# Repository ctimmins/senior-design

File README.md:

# SENIOR DESIGN Fall 2014 - Winter 2015
##Various files for the projects throughout senior design
###Agricultural Monitoring System
Our senior design project
###Magnetometer
A silly little project in Fall quarter to establish i2c communication between a magnetometer and psoc5 dev kit
###Check out my [website](www.chadtimmins.com) for further updates!

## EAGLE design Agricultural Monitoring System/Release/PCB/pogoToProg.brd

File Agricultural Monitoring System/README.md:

<!-- START doctoc generated TOC please keep comment here to allow auto update -->
<!-- DON'T EDIT THIS SECTION, INSTEAD RE-RUN doctoc TO UPDATE -->
**Table of Contents**  *generated with [DocToc](https://github.com/thlorenz/doctoc)*

- [System for Temperature and Evapotranspiration Monitoring (STEM)](#system-for-temperature-and-evapotranspiration-monitoring-stem)
  - [Abstract](#abstract)
  - [Marketing Video](#marketing-video)
  - [Features/Components](#featurescomponents)
      - [PSoC5](#psoc5)
      - [Soil Sensors](#soil-sensors)
      - [Infrared Sensor](#infrared-sensor)
      - [XBee Wireless Radio](#xbee-wireless-radio)
      - [Battery System](#battery-system)
      - [Low Power Consumption](#low-power-consumption)
      - [Beaglebone Black](#beaglebone-black)
      - [Data Store](#data-store)
      - [Web Application and Synchronized Data](#web-application-and-synchronized-data)
      - [Analytics Framework](#analytics-framework)
  - [Future Improvements](#future-improvements)
  - [User Manual](#user-manual)
      - [STEM](#stem)
      - [Beaglebone](#beaglebone)
      - [Firebase](#firebase)
      - [Web Application](#web-application)

<!-- END doctoc generated TOC please keep comment here to allow auto update -->

#System for Temperature and Evapotranspiration Monitoring (STEM)

##Abstract
Monitoring plant health and conserving water are two important considerations in regards to agriculture, especially given the current drought. Plants take in water through rainfall and regular watering and lose water through transpiration. If growers can quantify the amount of water that is available to the plant and how much the plant loses through transpiration, they can irrigate more efficiently. STEM accomplishes both of these goals by monitoring soil moisture and temperature at different depths in the ground around a plant.  STEM also observes the leaf temperature of the plant, which correlates to whether or not the stomata are opened or closed and thus whether or not water is evaporating from the leaves.

The board in the field sends the captured data wirelessly to a coordinator which then uploads the data to a remote database.  From this point, growers can view the data using our web application on a computer or tablet.

##Marketing Video

##Drawings of Systems and Subsystems

##Features/Components
####PSoC5
32 bit ARM Cortex M0 based programmable system on chip a.k.a. the brains of each node.
####Soil Sensors
The multi-level installation of subterraneous sensors gives the user a soil moisture and temperature profile and is useful for monitoring the progression of the water-front.  In other words, our system is able to track how water flows through soil and the conditions that cause it do so.  The soil moisture sensors use transmission line techniques to acquire volumetric water content and are immune to inaccurate measurements due to varying levels of salinity.
####Infrared Sensor
The mounted infrared camera gives the user the ability to detect changes in leaf temperature as a function of time. This is used to determine when the stomates in the leaf closes in the day, which marks the point where the plant stops losing water.
####XBee Wireless Radio
XBee radios are low energy, low bandwidth radios that have a range of around 300 feet.
####Battery System
The device is powered by a 2500 mAh Li-po battery. The battery can be recharged through an external solar panel or a USB phone charger. A analog to digital converter is placed to measure the health of the battery, thereby alerting the user that the battery is low.
####Low Power Consumption
Sleep timers were implemented to reduce overall power consumption. The board itself wakes up roughly every 4 seconds, but only takes and transmits measurements periodically. The frequency of message transmittance is user defined and can easily be adjusted depending on the application.
####Beaglebone Black
We used TI’s Beaglebone Black as the XBee coordinator and internet gateway. An XBee radio was mounted to the Beaglebone and Python scripts were developed to handle all communication to and from the wireless sensors. It also maintains information about multiple nodes such as battery status, and various IR configuration settings. Additional scripts were developed for uploading our data to a secure database (Firebase).
The decision to go with a linux micro computer over Digi’s ConnectPort and proprietary Device Cloud was due to the difficulty of integrating a custom user interface with Digi’s services.
####Data Store
We used Firebase to collect and manage all data.  Firebase was chosen for its simplicity in uploading and retrieving data.  It also provides an easy to use dashboard to manage, view, and download all data.
####Web Application and Synchronized Data
Our web application, along with Firebase as a backend, serves as a simple alternative to Etherios Device Cloud.  Firebase and the relevant javascript API’s allow for real time data synchronization across devices.  This means the user can see live updates of sensor data without having to refresh the page. 
####Analytics Framework
TBD

##Future Improvements

##User Manual
####STEM

####Beaglebone

####Firebase

####Web Application

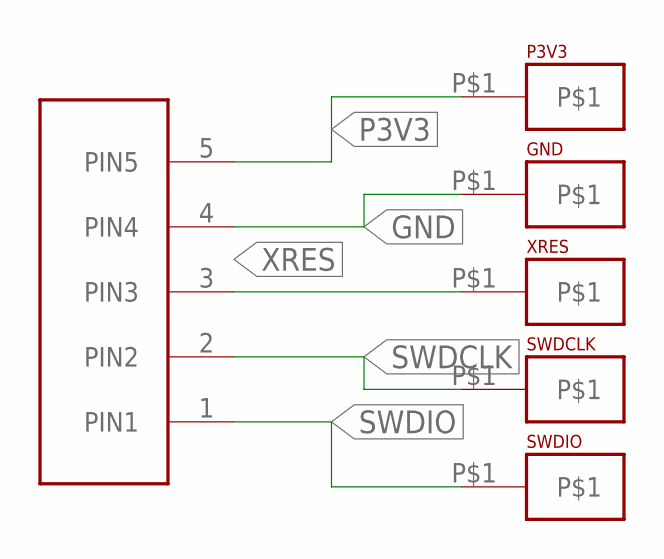
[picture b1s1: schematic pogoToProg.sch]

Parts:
GND: POGO-MATING
P3V3: POGO-MATING
SWDCLK: POGO-MATING
SWDIO: POGO-MATING
U$1: HEADER-5; NON-5
XRES: POGO-MATING

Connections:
GND: GND.P$1, U$1.4 (PIN4)
P3V3: P3V3.P$1, U$1.5 (PIN5)
SWDCLK: SWDCLK.P$1, U$1.2 (PIN2)
SWDIO: SWDIO.P$1, U$1.1 (PIN1)
XRES: U$1.3 (PIN3), XRES.P$1

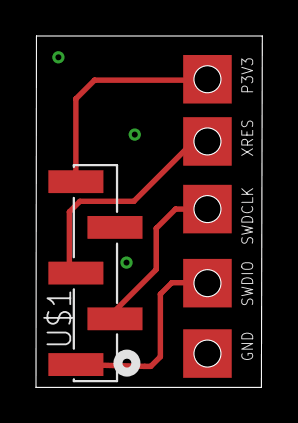
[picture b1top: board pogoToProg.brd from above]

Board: 2 copper layers, 12.6 x 19.5 mm, 6 parts (0 on the bottom side), 5 nets.

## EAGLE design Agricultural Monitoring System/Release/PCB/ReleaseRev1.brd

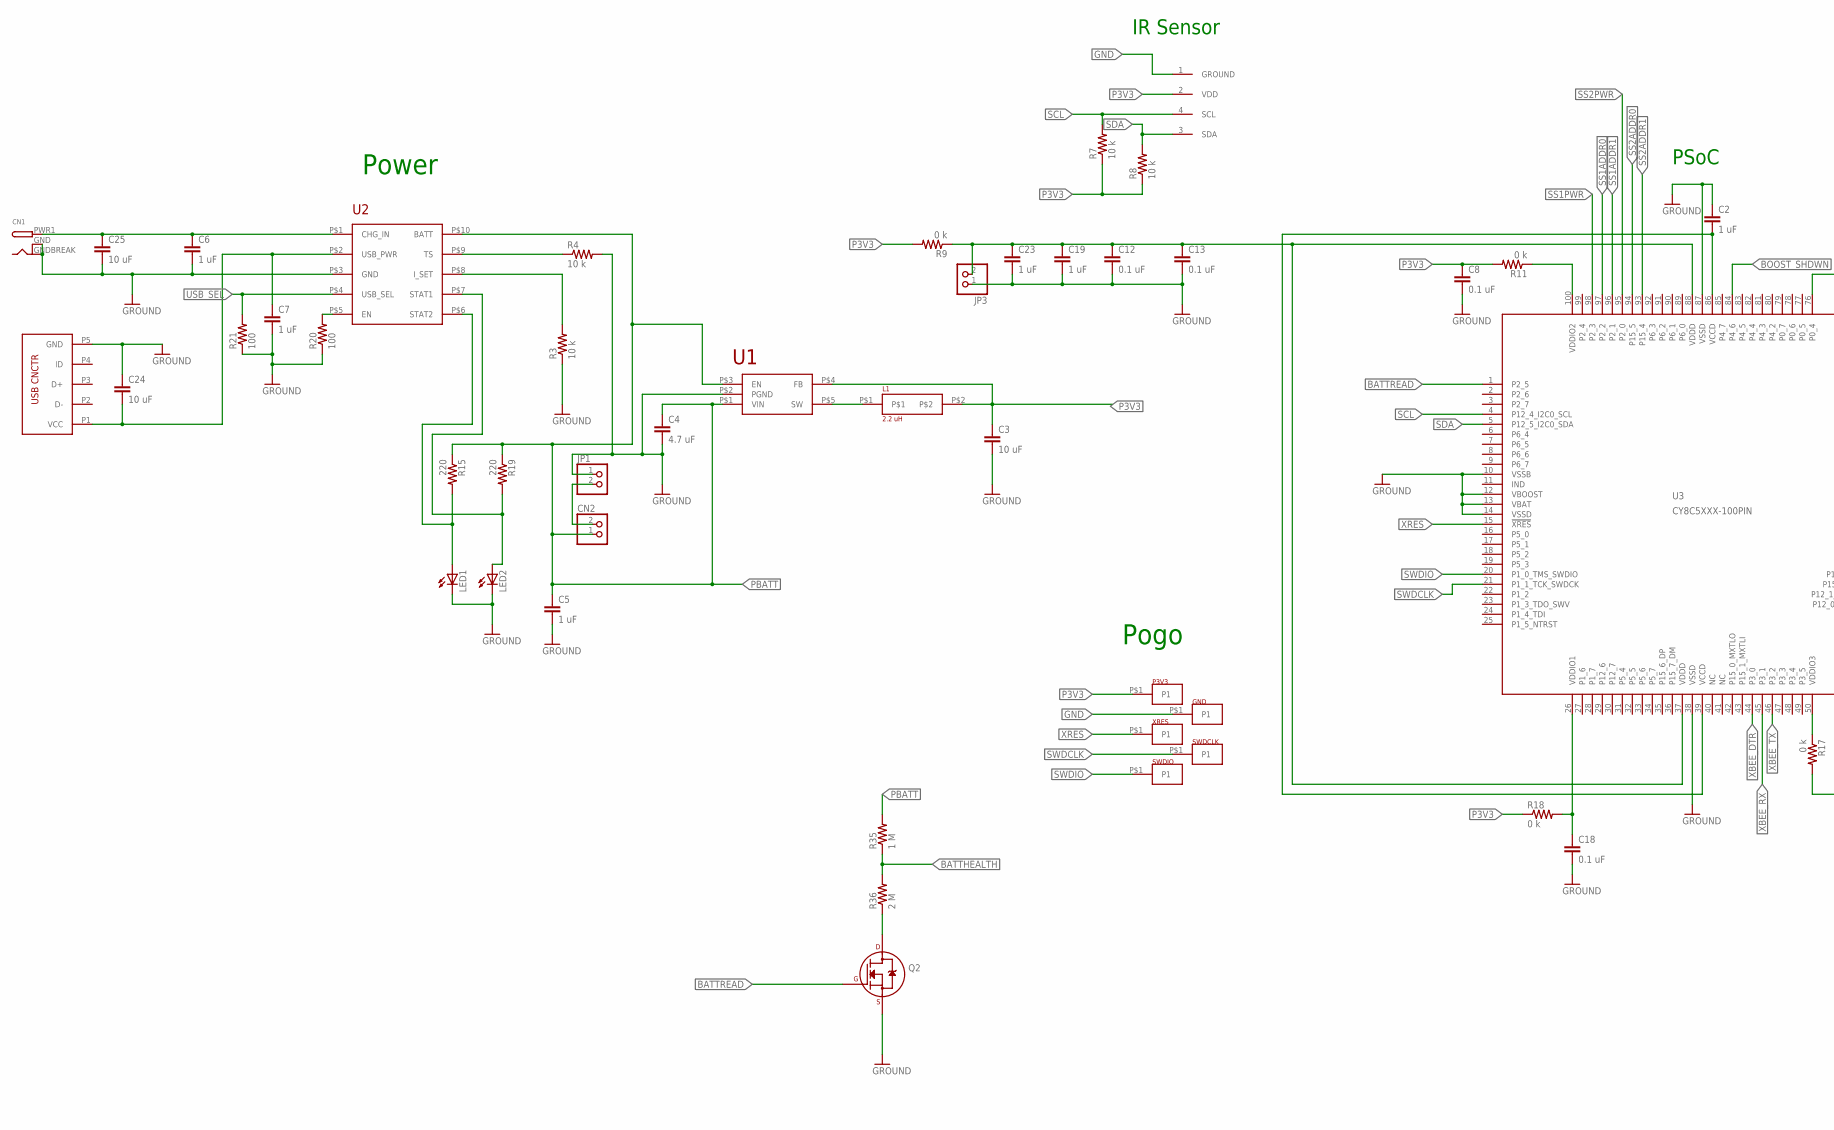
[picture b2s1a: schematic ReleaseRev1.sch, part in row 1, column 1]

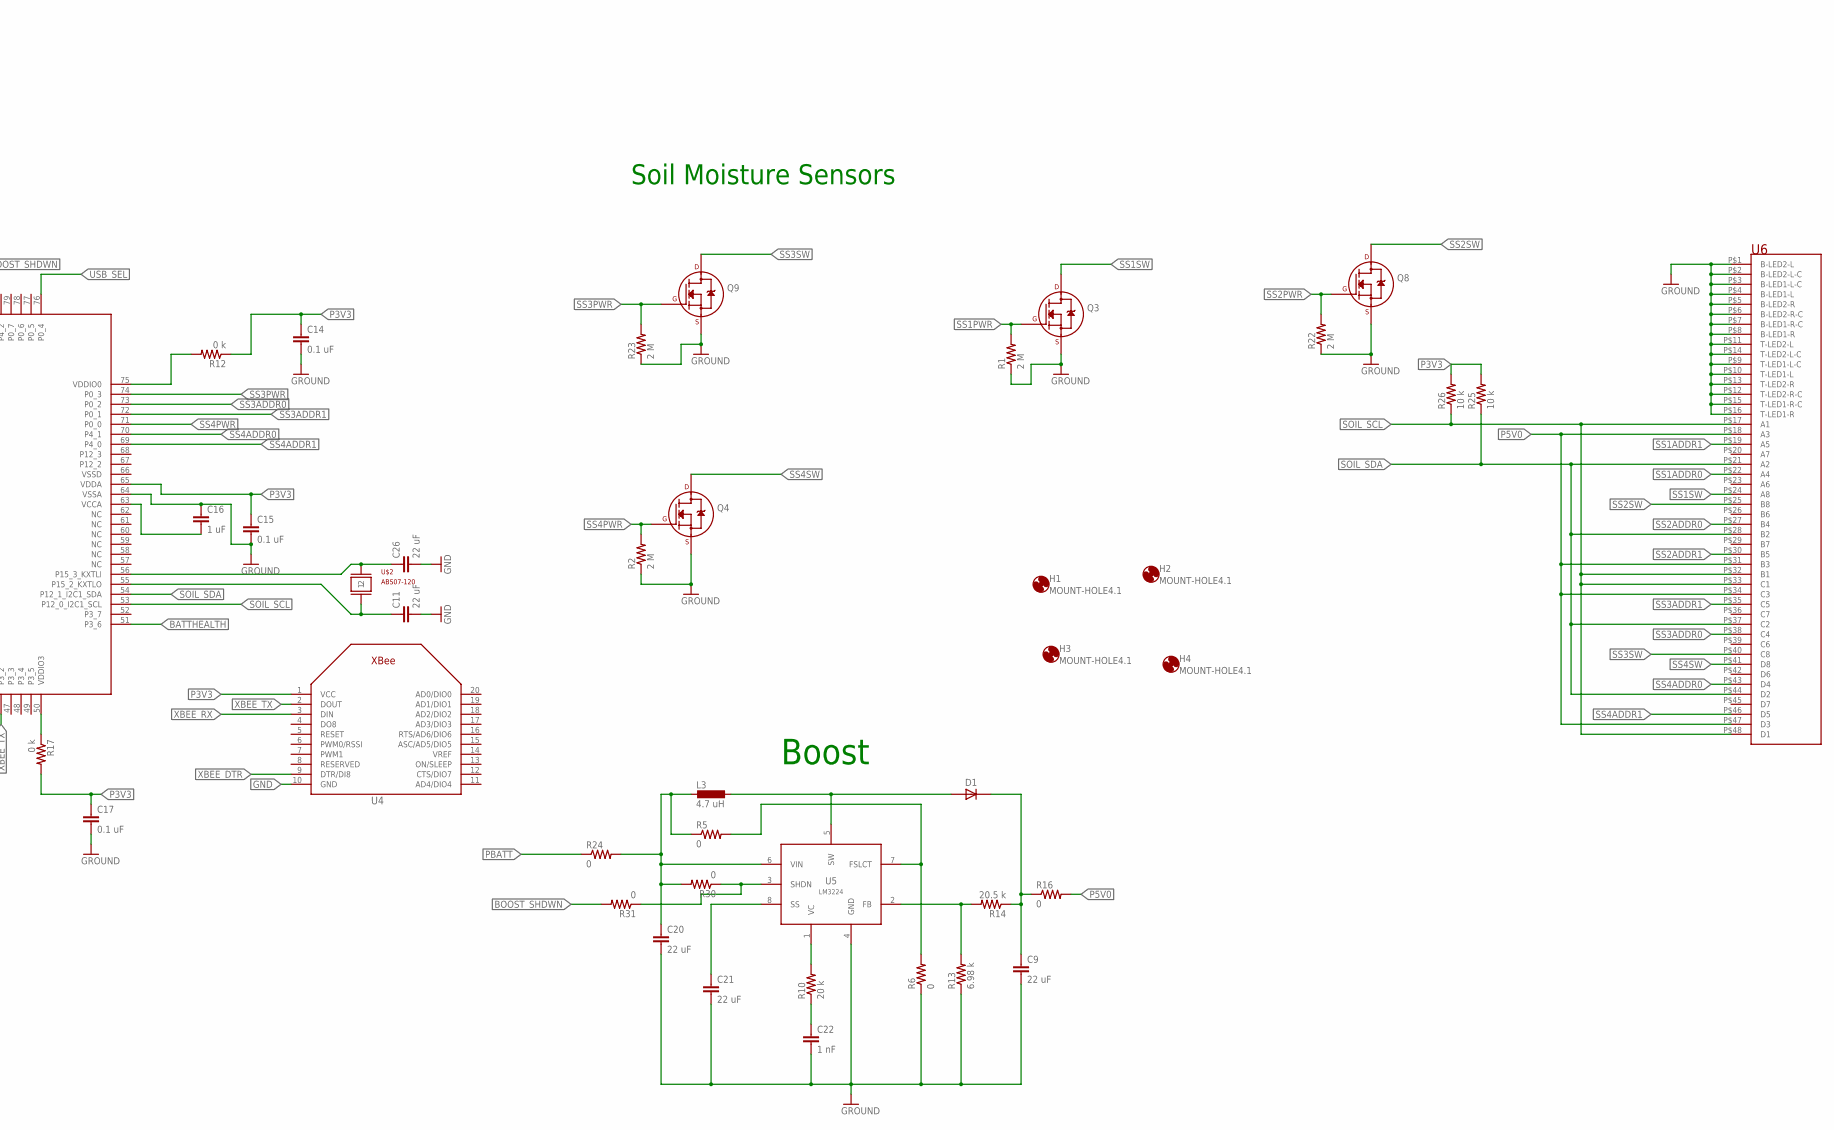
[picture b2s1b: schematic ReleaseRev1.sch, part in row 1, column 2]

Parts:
C2, C5, C6, C7, C16, C19, C23: 1 uF; 0603
C3, C24, C25: 10 uF; 0603
C4: 4.7 uF; 0603
C8, C12, C13, C14, C15, C17, C18: 0.1 uF; 0603
C9, C11, C20, C21, C26: 22 uF; 0603
C22: 1 nF; 0603
CN1: DCBARRELSMT; DCJACK_2MM_SMT
CN2: JST_2PIN-SMT-RA; JST-PH-2-SMT-RA
D1: DIODE; 0603-LED
GND: POGO-MOUNTING
H1, H2, H3, H4: MOUNT-HOLE4.1; 4,1
IRSENSOR: TO39
JP1, JP3: PINHD-1X2; 1X02
L1: LPO3310
L3: 4.7 uH; DO3316P
LED1, LED2: LEDCHIP-LED0603; CHIP-LED0603
P3V3: POGO-MOUNTING
Q2, Q3, Q4, Q8, Q9: 2N7000_SOT23; SOT-23
R1, R2, R22, R23, R36: 2 M; 0603
R3, R4, R7, R8, R25, R26: 10 k; 0603
R5, R6, R30, R31: 0; 0603
R9, R11, R12, R17, R18: 0 k; 0603
R10: 20 k; 0603
R13: 6.98 k; 0603
R14: 20.5 k; 0603
R15, R19: 220; 0603
R16, R24: 0; R2010
R20, R21: 100; 0603
R35: 1 M; 0603
SWDCLK: POGO-MOUNTING
SWDIO: POGO-MOUNTING
U1: LM3671-407564
U2: LM3658
U3: CY8C5XXX-100PIN; TQFP-14X14-100
U4: XBEE
U5: LM3224; MSOP-8
U6: RJSAE-5380-04
U$1: FCI10118192-0001LF
U$2: ABS07-120; 2-SMD
XRES: POGO-MOUNTING

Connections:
BATTHEALTH: R35.1, R36.2, U3.51 (P3_6)
BATTREAD: Q2.1 (G), U3.1 (P2_5)
BOOST_SHDWN: R31.2, U3.84 (P4_6)
GND: C2.1, C3.2, C4.2, C5.2, C6.2, C7.2, C8.2, C9.2, C11.2, C12.2, C13.2, C14.2, C15.2, C16.1, C17.2, C18.2, C19.2, C20.2, C21.2, C22.2, C23.2, C24.1, C25.2, C26.2, CN1.GND (GNDBREAK), CN1.GNDBREAK (GND), GND.P$1, IRSENSOR.1 (GROUND), JP1.1, JP3.1, LED1.C, LED2.C, Q2.2 (S), Q3.2 (S), Q4.2 (S), Q8.2 (S), Q9.2 (S), R1.1, R2.1, R3.1, R4.2, R6.1, R13.1, R20.1, R21.1, R22.1, R23.1, U1.P$2 (PGND), U2.P$3 (GND), U3.10 (VSSB), U3.12 (VBOOST), U3.13 (VBAT), U3.14 (VSSD), U3.38 (VSSD), U3.64 (VSSA), U3.87 (VSSD), U4.10 (GND), U5.4 (GND), U6.P$1 (B-LED2-L), U6.P$2 (B-LED2-L-C), U6.P$3 (B-LED1-L-C), U6.P$4 (B-LED1-L), U6.P$5 (B-LED2-R), U6.P$6 (B-LED2-R-C), U6.P$7 (B-LED1-R-C), U6.P$8 (B-LED1-R), U6.P$9 (T-LED1-L-C), U6.P$10 (T-LED1-L), U6.P$11 (T-LED2-L), U6.P$12 (T-LED2-R-C), U6.P$13 (T-LED2-R), U6.P$14 (T-LED2-L-C), U6.P$15 (T-LED1-R-C), U6.P$16 (T-LED1-R), U$1.P5 (GND)
unnamed: R20.2, U2.P$5 (EN)
unnamed: R3.2, U2.P$8 (I_SET)
unnamed: C21.1, U5.8 (SS)
unnamed: C26.1, U3.56 (P15_3_KXTLI), U$2.1
unnamed: C6.1, C25.1, CN1.PWR1 (PWR), U2.P$1 (CHG_IN)
unnamed: C18.1, R18.2, U3.26 (VDDIO1)
unnamed: D1.A, L3.2, U5.5 (SW)
unnamed: R4.1, U2.P$9 (TS)
unnamed: R10.2, U5.1 (VC)
unnamed: CN2.2 (1), JP1.2
unnamed: C22.1, R10.1
unnamed: R13.2, R14.2, U5.2 (FB)
unnamed: C2.2, U3.39 (VCCD), U3.86 (VCCD)
unnamed: Q2.3 (D), R36.1
unnamed: C16.2, U3.63 (VCCA)
unnamed: R5.2, R6.2, U5.7 (FSLCT)
unnamed: C11.1, U3.55 (P15_2_KXTLO), U$2.2
unnamed: R12.2, U3.75 (VDDIO0)
unnamed: R11.1, U3.100 (VDDIO2)
unnamed: C12.1, C13.1, C19.1, C23.1, JP3.2, R9.1, U3.37 (VDDD), U3.88 (VDDD)
unnamed: R17.1, U3.50 (VDDIO3)
unnamed: LED2.A, R19.2, U2.P$7 (STAT1)
unnamed: LED1.A, R15.2, U2.P$6 (STAT2)
unnamed: L1.P$1, U1.P$5 (SW)
unnamed: R30.1, R31.1, U5.3 (SHDN)
P: C20.1, L3.1, R5.1, R24.2, R30.2, U5.6 (VIN)
P3V3: C3.1, C8.1, C14.1, C15.1, C17.1, IRSENSOR.2 (VDD), L1.P$2, P3V3.P$1, R7.1, R8.1, R9.2, R11.2, R12.1, R17.2, R18.1, R25.2, R26.2, U1.P$4 (FB), U3.65 (VDDA), U4.1 (VCC)
P5: C9.1, D1.C, R14.1, R16.1
P5V0: R16.2, U6.P$18 (A3), U6.P$31 (B3), U6.P$34 (C3), U6.P$47 (D3)
PBATT: C4.1, C5.1, CN2.1 (2), R15.1, R19.1, R24.1, R35.2, U1.P$1 (VIN), U1.P$3 (EN), U2.P$10 (BATT)
SCL: IRSENSOR.4 (SCL), R7.2, U3.4 (P12_4_I2C0_SCL)
SDA: IRSENSOR.3 (SDA), R8.2, U3.5 (P12_5_I2C0_SDA)
SOIL_SCL: R26.1, U3.53 (P12_0_I2C1_SCL), U6.P$17 (A1), U6.P$32 (B1), U6.P$33 (C1), U6.P$48 (D1)
SOIL_SDA: R25.1, U3.54 (P12_1_I2C1_SDA), U6.P$21 (A2), U6.P$28 (B2), U6.P$37 (C2), U6.P$44 (D2)
SS1ADDR0: U3.97 (P2_2), U6.P$22 (A4)
SS1ADDR1: U3.96 (P2_1), U6.P$19 (A5)
SS1PWR: Q3.1 (G), R1.2, U3.98 (P2_3)
SS1SW: Q3.3 (D), U6.P$24 (A8)
SS2ADDR0: U3.94 (P15_5), U6.P$27 (B4)
SS2ADDR1: U3.93 (P15_4), U6.P$30 (B5)
SS2PWR: Q8.1 (G), R22.2, U3.95 (P2_0)
SS2SW: Q8.3 (D), U6.P$25 (B8)
SS3ADDR0: U3.73 (P0_2), U6.P$38 (C4)
SS3ADDR1: U3.72 (P0_1), U6.P$35 (C5)
SS3PWR: Q9.1 (G), R23.2, U3.74 (P0_3)
SS3SW: Q9.3 (D), U6.P$40 (C8)
SS4ADDR0: U3.70 (P4_1), U6.P$43 (D4)
SS4ADDR1: U3.69 (P4_0), U6.P$46 (D5)
SS4PWR: Q4.1 (G), R2.2, U3.71 (P0_0)
SS4SW: Q4.3 (D), U6.P$41 (D8)
SWDCLK: SWDCLK.P$1, U3.21 (P1_1_TCK_SWDCK)
SWDIO: SWDIO.P$1, U3.20 (P1_0_TMS_SWDIO)
USB: C7.1, C24.2, U2.P$2 (USB_PWR), U$1.P1 (VCC)
USB_SEL: R21.2, U2.P$4 (USB_SEL), U3.76 (P0_4)
XBEE_DTR: U3.44 (P3_0), U4.9 (DTR/DI8)
XBEE_RX: U3.45 (P3_1), U4.3 (DIN)
XBEE_TX: U3.46 (P3_2), U4.2 (DOUT)
XRES: U3.15 (!XRES!), XRES.P$1

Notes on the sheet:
PSoC
IR Sensor
Boost
Pogo
Power
Soil Moisture Sensors

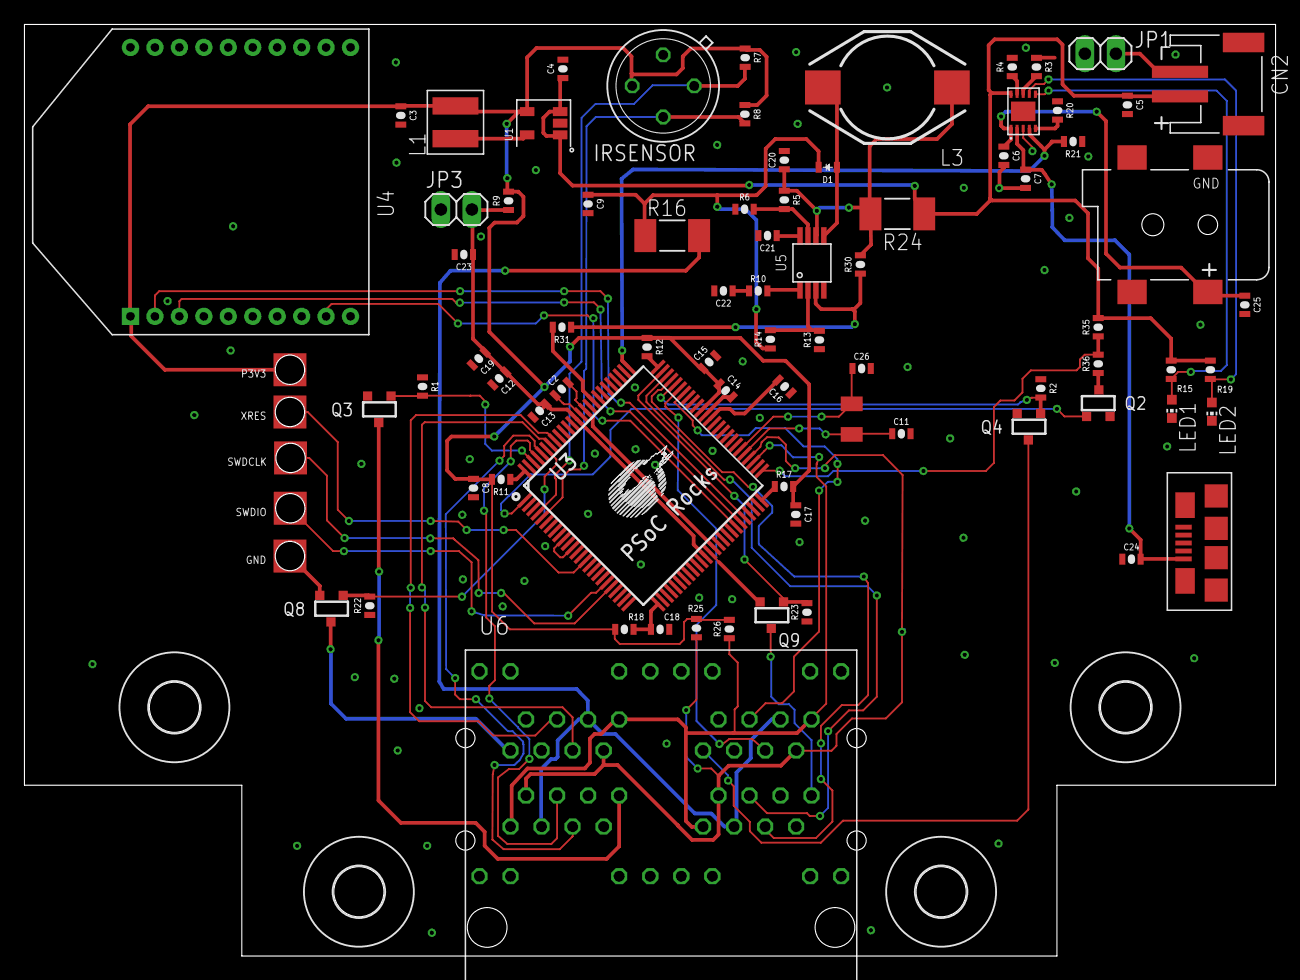
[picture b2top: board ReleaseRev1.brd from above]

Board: 2 copper layers, 102.3 x 76.2 mm, 86 parts (0 on the bottom side), 62 nets.

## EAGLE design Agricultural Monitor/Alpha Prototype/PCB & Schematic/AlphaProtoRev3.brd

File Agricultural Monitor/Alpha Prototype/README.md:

#Alpha Prototype
##The first hardware prototype of the agricultural monitoring system
###Bill of Materials

###PCB Layout

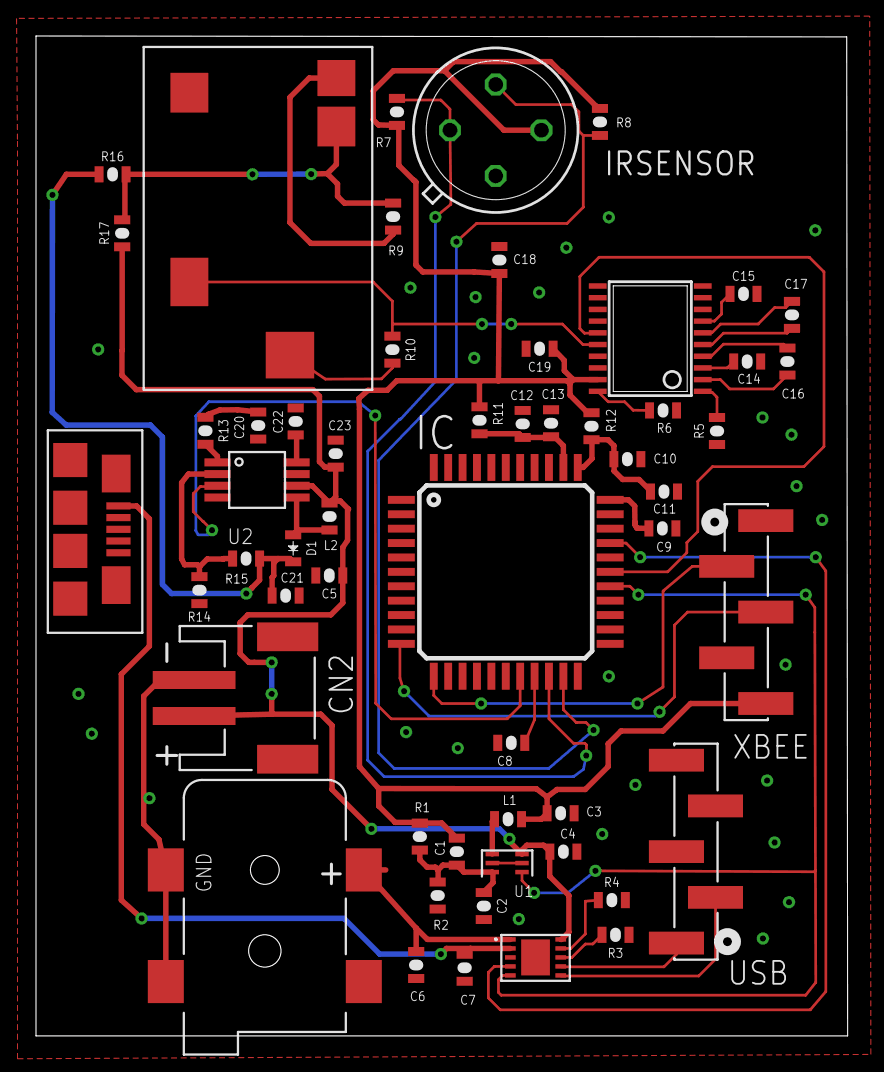
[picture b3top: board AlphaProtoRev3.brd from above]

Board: 2 copper layers, 45.1 x 55.5 mm, 55 parts (0 on the bottom side), 41 nets.

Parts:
C1: 0.8 pF; 0603
C2: 33 pF; 0603
C3, C21: 10 uF; 0603
C4: 4.7 uF; 0603
C5, C6, C7, C10, C13, C19: 1 uF; 0603
C8, C9, C11, C12, C14, C15, C16, C17, C18: 0.1 uF; 0603
C20: 1 nF; 0603
C22, C23: 22 uF; 0603
CN1: DCJACK_2MM_SMT
CN2: JST-PH-2-SMT-RA
D1: DIODE; 0603-LED
IC: PSOC4FP; TQFP44
IC1: MAX3222CUP; TSSOP20
IRSENSOR: TO39
L1: 2.2 uH; 0603
L2: 4.7 uH; 0603
R1: 562; 0603
R2: 100; 0603
R3, R4, R5, R6, R7, R8: 10 k; 0603
R9, R10, R11, R12, R16, R17: 0 k; 0603
R13: 20 k; 0603
R14: 6.98 k; 0603
R15: 20.5 k; 0603
U1: LM3671-407564
U2: LM3224; MSOP-8
U$2: AUDIOJACK
U$4: LM3658
U$7: FCI10118192-0001LF
USB: HEADER-5; NON-5
XBEE: HEADER-5; NON-5

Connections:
BOOSTOUT: C21.1, D1.C, R15.1, R16.1
BSTSHDWN: IC.18, U2.3
DATA: IC1.16, R10.1, U$2.P$3
DATA_R: IC.28, IC1.15
ENREG: IC.27, U1.P$1, U$4.P$5
GND: C2.2, C3.2, C4.2, C5.2, C6.2, C7.2, C8.2, C9.2, C10.2, C11.2, C12.2, C13.2, C14.2, C15.2, C18.2, C19.2, C20.2, C21.2, C22.2, C23.2, CN1.GND, CN1.GNDBREAK, CN2.2, IC.1, IC.10, IC.36, IC1.18, IRSENSOR.1, R2.2, R3.1, R4.2, R5.1, R6.2, R14.1, U1.P$2, U1.P$5, U2.4, U2.7, U$2.P$1, U$4.P$3, U$7.P5, XBEE.4
unnamed: C4.1, C5.1, C23.1, CN2.1, L2.1, R17.1, U1.P$3, U2.6, U$4.P$10
unnamed: R3.2, U$4.P$8
unnamed: L1.1, U1.P$4
unnamed: IC1.1, R5.2
unnamed: C6.1, CN1.PWR1, U$4.P$1
unnamed: C1.1, C2.1, R1.2, R2.1, U1.P$6
unnamed: C7.1, U$4.P$2, U$7.P1
unnamed: R4.1, U$4.P$9
unnamed: R13.2, U2.1
unnamed: C12.1, C13.1, IC.35, R11.2
unnamed: U$4.P$6, USB.2
unnamed: U$4.P$7, USB.1
unnamed: C17.2, IC1.6
unnamed: C8.1, IC.19
unnamed: C9.1, IC.33
unnamed: C17.1, IC1.5
unnamed: R9.2, U$2.P$4
unnamed: R10.2, U$2.P$5
unnamed: C16.2, IC1.4
unnamed: C16.1, IC1.2
unnamed: C14.1, IC1.3
unnamed: C15.1, IC1.7
unnamed: IC1.20, R6.1
unnamed: C10.1, C11.1, IC.34, R12.2
unnamed: C20.1, R13.1
unnamed: D1.A, L2.2, U2.5
unnamed: R9.1, R16.2, R17.2, U$2.P$2
unnamed: R14.2, R15.2, U2.2
unnamed: C22.1, U2.8
P3V3: C1.2, C3.1, C18.1, C19.1, IC1.19, IRSENSOR.2, L1.2, R1.1, R7.1, R8.1, R11.1, R12.1, XBEE.5
SCL: IC.20, IRSENSOR.4, R7.2
SDA: IC.21, IRSENSOR.3, R8.2
USB_SEL: IC.30, U$4.P$4
XBEE_RX: IC.12, XBEE.2
XBEE_TX: IC.11, XBEE.3

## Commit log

2014-12-04 cleaning up previous git project
2014-12-04 modified gitignore for .cyprj
2014-12-04 added neccessary files
2014-12-04 latest driver
2014-12-05 Configurable data sampling rate. Added table for logging data points
2014-12-05 updated main and MAG3110 driver for register write offset
2014-12-18 Uploaded Alpha Prototype PCB
2014-12-18 Added Bill of Materials and README.md
2014-12-18 added a few changes
    Rev 1.0.0
2014-12-18 Revert 75fc657..a2bee14
    This rolls back to commit 75fc657718548f20888040a98fae5aee6c9d0f2b.
2014-12-18 Added screenshot of top design pcbs
2014-12-18 Changed README.md to use board layout
2014-12-18 adding bom table to read
2014-12-18 added bom png
2014-12-18 edited readme
2014-12-18 updated ag monitor description
2014-12-18 fixed ul
2014-12-25 fixed unordered list of tasks
2014-12-25 fixed link on home page
2014-12-25 Updated description with main components
2014-12-25 Changed name from Agricultural Monitor
2014-12-25 fixed schematic links in alpha proto
2014-12-31 Added driver folder for sensor and post drivers
2015-01-05 started SDI-12 driver for PSoC to Decagon sensor communication
2015-01-05 skeleton driver. Is git push necessary?
2015-01-07 modified .gitignore to exclude and documents or pdf's pertinent to the project
2015-01-07 on a second thought, may be useful to have all documents available to anyone reading this
2015-01-07 Added Decagon 5TM user manual and SDI-12 documentation to Documents/Examples
2015-01-07 changed name of documents folder
2015-01-08 Added description of data logger
2015-01-08 hello world
2015-01-08 started creating utility functions
2015-01-08 forgot to save
2015-01-08 Erik Says Hello
    Testing git
2015-01-08 david is on github
2015-01-09 Implemented CRC function in util.h
2015-01-09 Decagon Simple Data Logger
2015-01-09 Deleted top of main
2015-01-10 Added Xbee Internet Gateway python scripts
2015-01-10 Added IR sensor to main components
2015-01-14 MLX Driver
    Only works for getting raw IR/Temperature data. Need to further process
    data on external program for useful information.
2015-01-15 Added sample java application for GUI. Moved MLX cypress project to proper folder under data logger
2015-01-15 removed copy of xig.py and added nic's python script for X2 and Sleep Cycle C code for PSOC 4100
2015-01-15 GUI component of Monitoring System
2015-01-15 ignore config file
2015-01-16 ConnectPort query state and query setting functions added
2015-01-16 separated app functionality from digi device commands and other functions
2015-01-20 client side authentication issues forced me to create a python application for using Device Cloud's API
2015-01-20 can query device settings, device status, and list all data streams
2015-01-21 added full stack Flask GUI.
2015-01-21 Implemented remote XBee AT parameter set and get functions
2015-01-21 Data stream manipulation functions added
2015-01-21 fixed python script comments
2015-01-22 integrated firebase with flask GUI
2015-01-23 modified url parameters to parse
2015-01-26 Added README to Flask GUI
2015-01-26 fixed python comment issues in nic's script
2015-02-06 Added beaglebone xbee. Rearranged GUI and general file structure. Will push to new repository for beaglebone. I did a bad job on this commit :(
2015-02-12 First push of stemGUI using firbase as backend
2015-02-13 changed method of iterating through snapshot using Firebase SDK
2015-02-13 redefined object for snapshot array
2015-02-13 html for showing values in each snapshot
2015-02-13 Added d3 dependency and new factory for parsing sensor node data
2015-02-13 Implemented removeRecord function in nodeParsing factory
2015-02-13 Added D3 factory, added findEntryByTime function to nodeParsing factory
2015-02-16 Added simple line chart directive and graphed hard coded data
2015-02-18 Updated main README and moved older GUI files into separate folder
2015-02-18 changed d3 service script source URL
2015-02-18 Changed Title
2015-02-18 Added link to other Repo in readme
2015-02-22 using angular-chart d3 directives and deleted previous d3 services
2015-02-22 Modified legend sass and deleted simple line chart directive
2015-02-22 added angular-chart css source
2015-02-22 fixed css build import
2015-02-22 hard coded more data for performance measurements
2015-02-24 PSOC5 sleep timer code
2015-02-24 Added UART for XBee tests
2015-02-26 synchronized data with collected sensor data stored in firebase
2015-02-26 added new page for leave IR profile
2015-02-27 deleted redundant firebase data tracking
2015-02-27 Beta main with correct formatting for beaglebone
2015-02-27 ughh
2015-03-02 Cant believe root url was source of bug
2015-03-03 modified main controller
2015-03-03 Added Beta PCB's
    So Jeff knows how to do it
2015-03-03 changed checksum parameter list
2015-03-05 Successfully implemented sleep
2015-03-07 updated angular fire and messed around with array syncs
2015-03-07 fixed missing data issue
2015-03-07 Changed html and put vwc and temp on same row
2015-03-07 added leaflet dependency and map
2015-03-08 reshuffled layout and can change data from leaflet markers
2015-03-10 style changes
2015-03-11 Added Release board psoc files
2015-03-11 changed some parameters for app
2015-03-12 added yahoo weather
2015-03-18 used doctoc to generate table of contents
2015-03-18 testing readme change
2015-03-18 Updated STEM readme
2015-03-18 lets try that again
2015-03-18 update read
2015-03-18 added marketing presentation
2015-03-18 ready update
2015-03-18 Put LINK to youtube marketing video in readme
2015-03-18 Forgot to update TOC
2015-03-18 missing period
2015-03-20 new logo
2015-03-27 Create Spring Quarter Work
